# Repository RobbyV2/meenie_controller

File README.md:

# Meenie Controller

Meenie is a USB-C controller board. The board has a Nordic nRF52840 microcontroller. The board has Bluetooth Low Energy, USB 2.0 data, and 15 GPIO breakout holes. The board has one red status LED and one reset switch. The board has three service lands for SWDIO, SWCLK, and +3V3.

<table>
<tr>
<td></td>
<td></td>
<td></td>
</tr>
</table>

## Specifications

| Item | Value |
|---|---|
| Board size | 13.570 x 9.435 mm |
| Copper layers | 8, in a 3+2+3 sequential HDI stack |
| Finished thickness | 0.991 mm, quoted as a nominal 1.0 mm |
| Microcontroller | Nordic nRF52840-QIAA, aQFN-73, on B.Cu |
| Connector | 16-position USB-C sink receptacle on F.Cu |
| Antenna | Locked track on the F.Cu layer at the west edge |
| Reset switch | C&K NanoT `GSNANOT000102` on B.Cu |
| Surface finish | ENIG |
| Panel | 5 x 7, 35 boards, 89.850 x 92.045 mm |

Read `docs/design.md` for the full stack table and the via inventory.

The short axis of the board is 9.435 mm. NextPCB, for example, has a minimum board size is 10 x 10 mm.

## Repository layout

- `hw/` holds the KiCad schematic, the board, the design rules, and the stack manifest.
- `lib/` holds the symbols, the footprints, and the 3D models.
- `scripts/` holds the release script, the panel tools, and the validation scripts.
- `fab/` holds the fabrication data, written by `scripts/release.sh`.
- `docs/` holds the design specification and the vendor order gate.
- `3d/` holds the 3D build script, the three renders, and the viewer page.

## Build the 3D output
```
python3 3d/build.py
```

## Build the fabrication tree
```
MEENIE_DRY_RUN=1 scripts/release.sh hw/meenie.kicad_pcb
```

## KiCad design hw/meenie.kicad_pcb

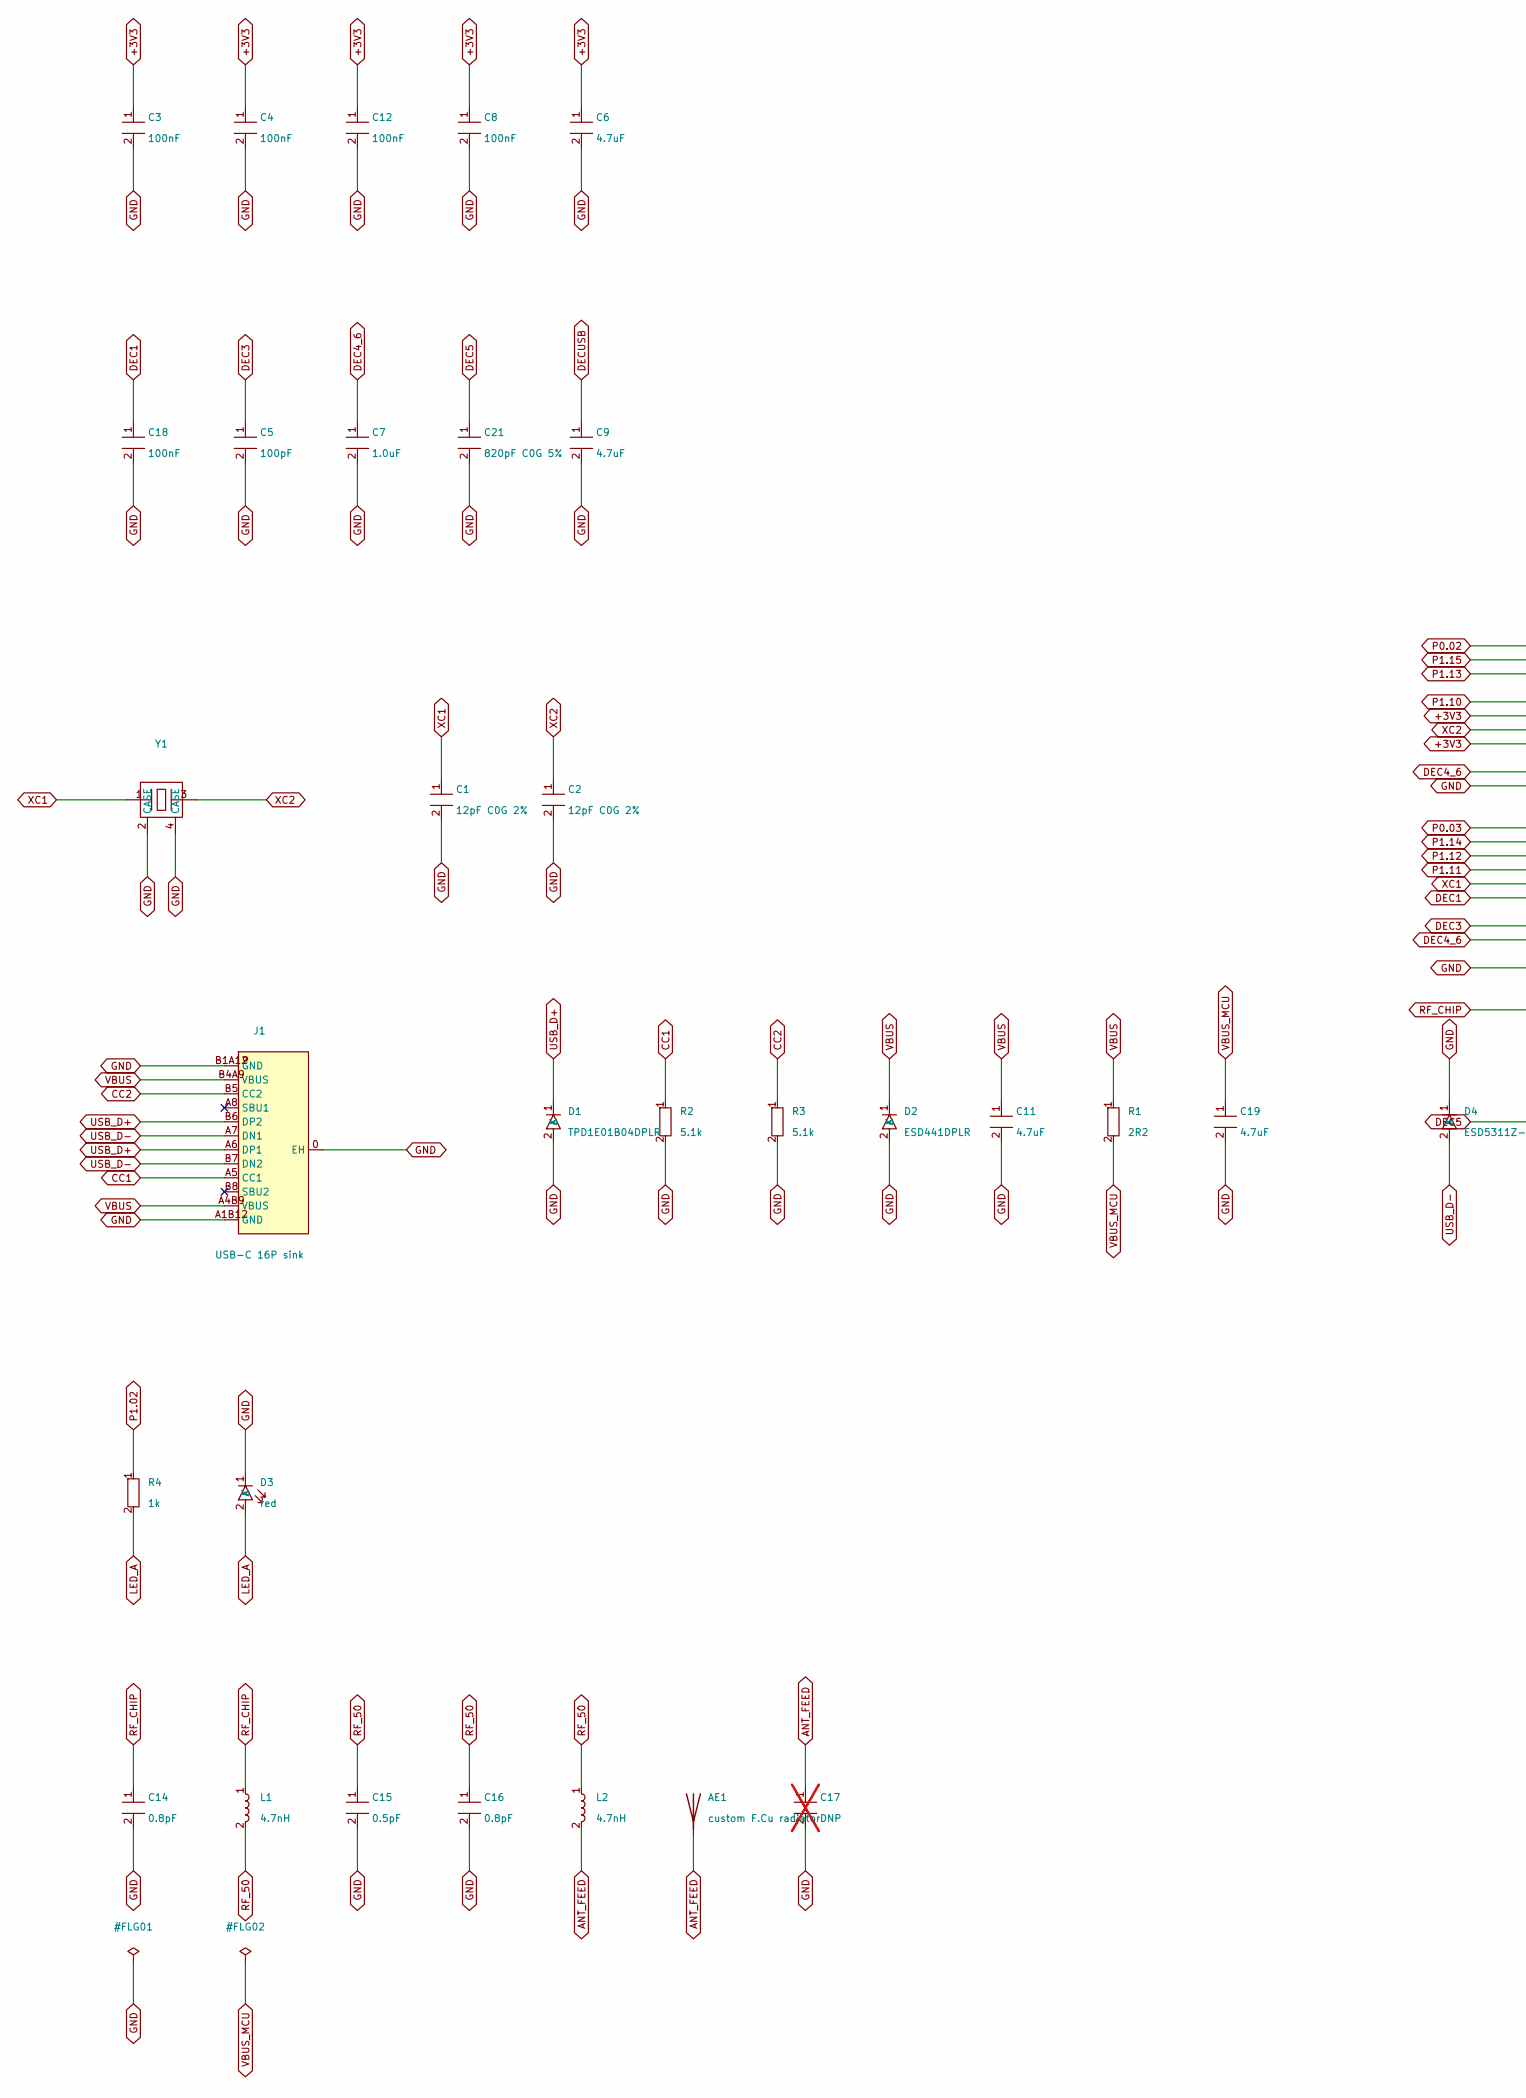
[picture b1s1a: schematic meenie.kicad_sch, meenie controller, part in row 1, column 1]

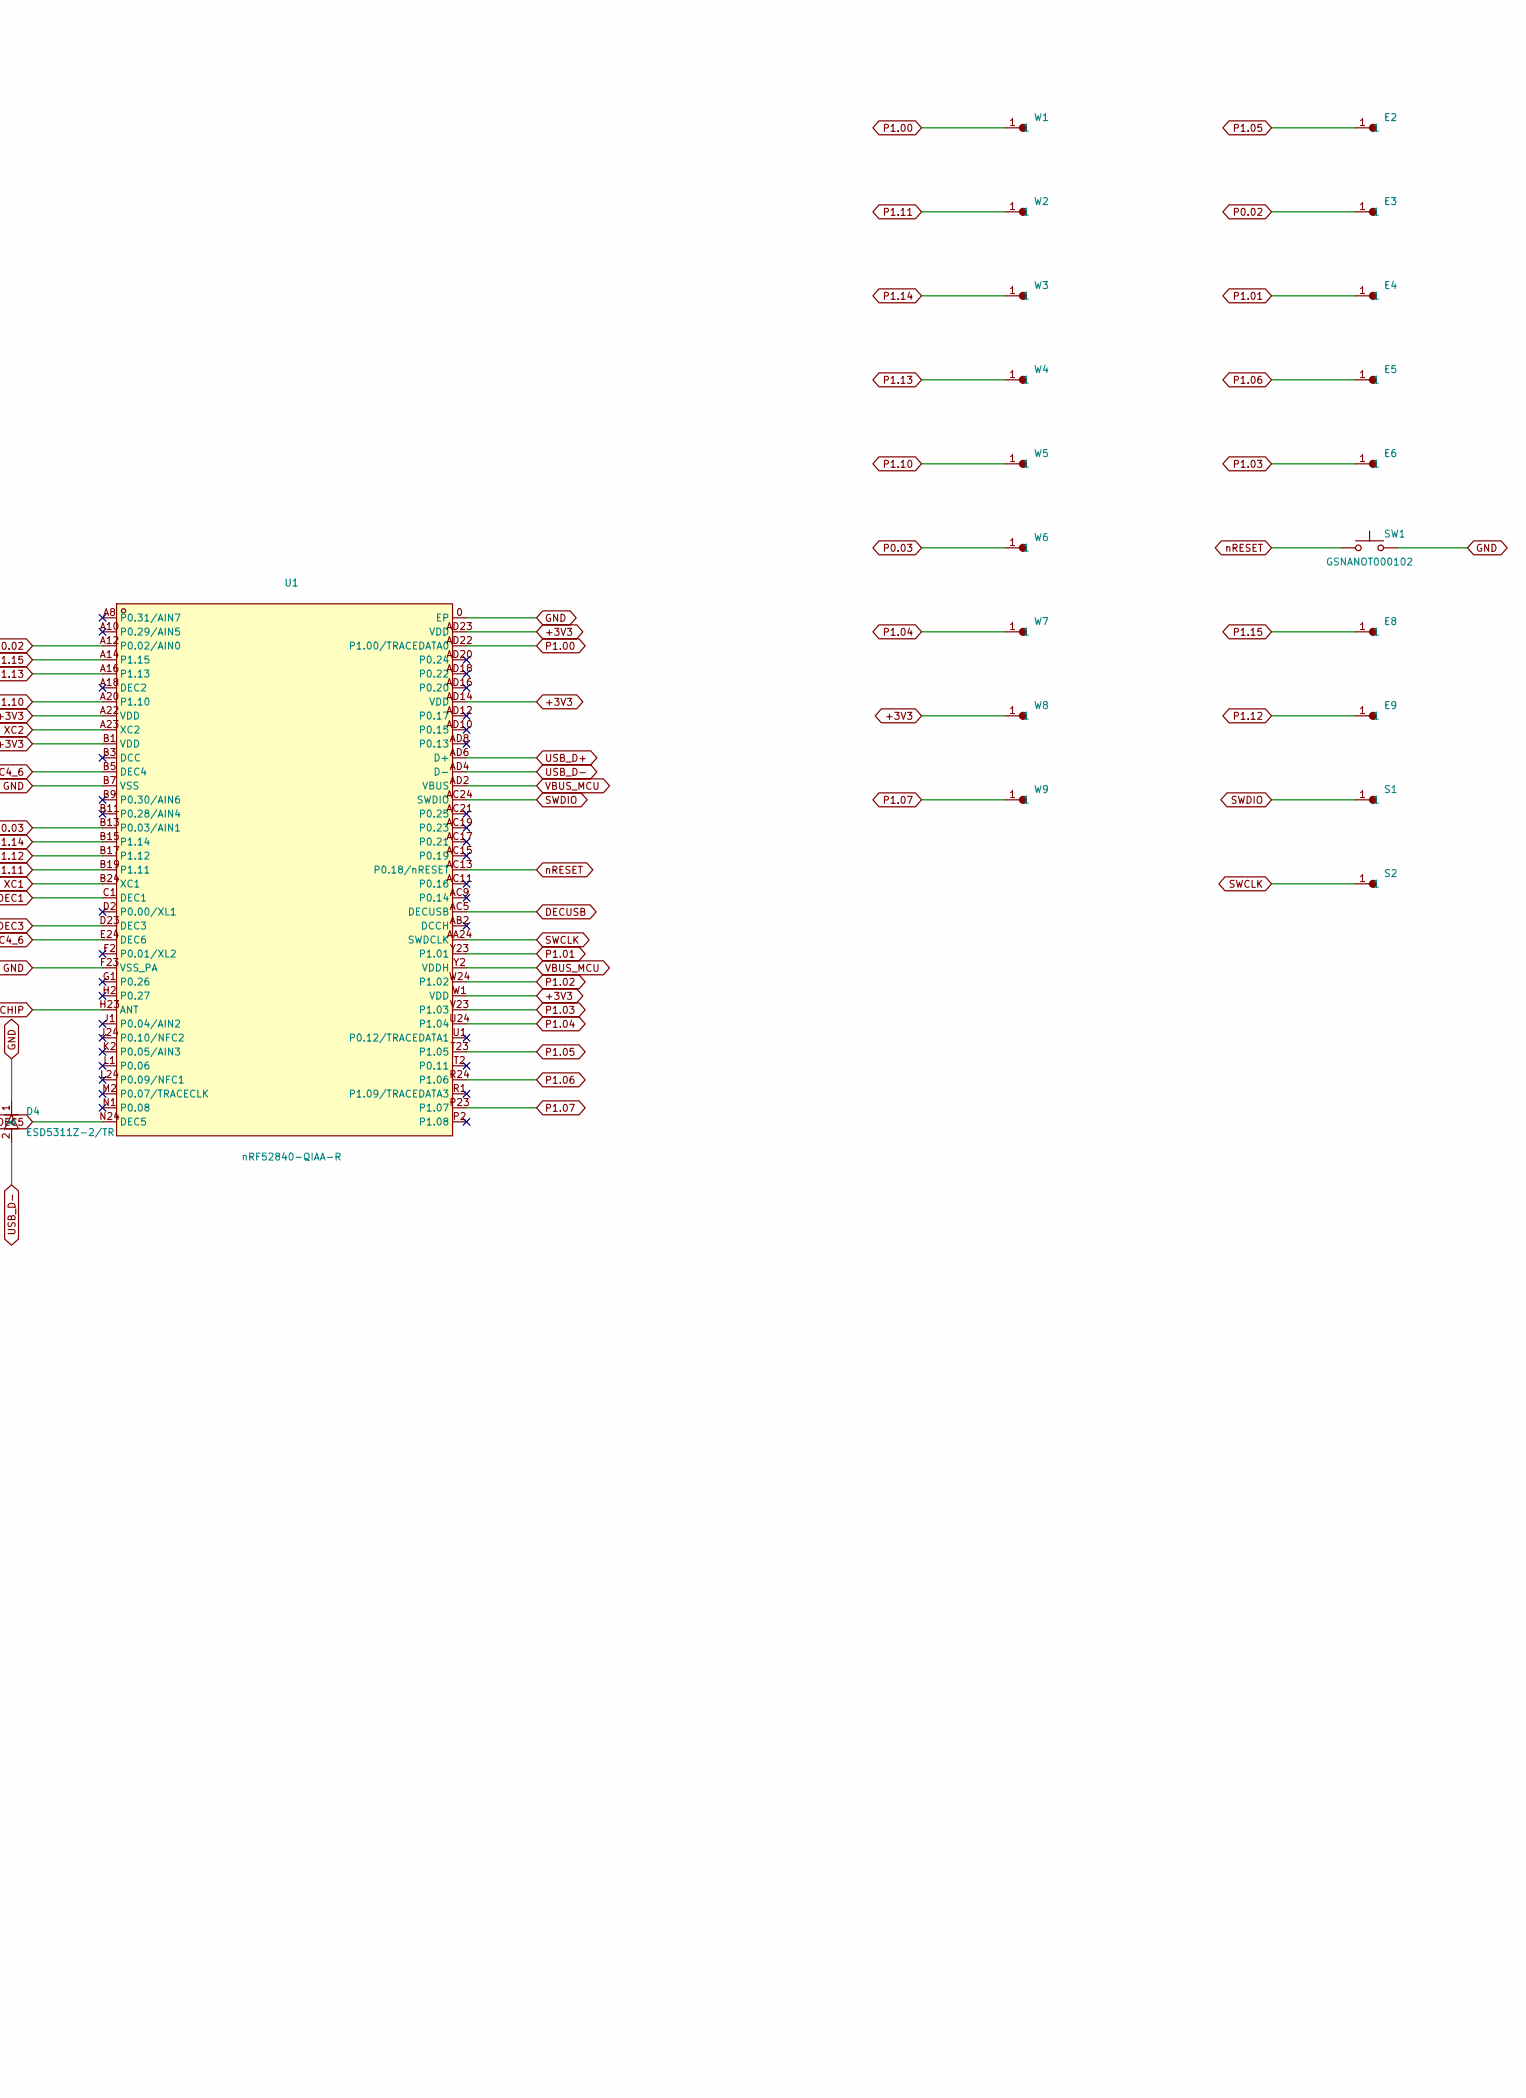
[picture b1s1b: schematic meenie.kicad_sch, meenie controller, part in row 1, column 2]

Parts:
AE1: custom F.Cu radiator
C1, C2: 12pF C0G 2%; C0201; MPN GRM0335C1H120GA01D; LCSC Part C161404
C3, C12, C18: 100nF; C0201; MPN GRM033C71C104KE14D; LCSC Part C85923
C4: 100nF; C0201_Murata_GRM033; MPN GRM033C71C104KE14D; LCSC Part C85923
C5: 100pF; C0201; MPN CC0201JRNPO9BN101; LCSC Part C272870
C6: 4.7uF; C0603; Manufacturer Part Number GRM188R61E475KE11D; LCSC Part C90057
C7: 1.0uF; C0402; MPN CL05A105KA5NQNC; LCSC Part C52923
C8: 100nF; C0402; Manufacturer Part Number CL05B104KO5NNNC; LCSC Part C1525
C9, C11: 4.7uF; C0603; MPN GRM188R61E475KE11D; LCSC Part C90057
C14, C16: 0.8pF; C0201; MPN GJM0335C1ER80WB01D; LCSC Part C408126
C15: 0.5pF; C0201; MPN GJM0335C1HR50WB01D; LCSC Part C237424
C17: DNP; C0201; LCSC Part NOT SELECTED; not fitted
C19: 4.7uF; C0402; Manufacturer Part Number CL05A475MO5NUNC; LCSC Part C318563
C21: 820pF C0G 5%; C0201; MPN GRM0335C1E821JA01D; LCSC Part C384953
D1: TPD1E01B04DPLR; ESD_X2SON_DPL; MPN TPD1E01B04DPLR; LCSC Part C1972949
D2: ESD441DPLR; ESD_X2SON_DPL; MPN ESD441DPLR; LCSC Part C22427765
D3: red; LED0402-R-RD_RED; MPN LTST-C281KRKT; LCSC Part C364556
D4: ESD5311Z-2/TR; ESD_DFN0603-2; MPN ESD5311Z-2/TR; LCSC Part C239819
E2, E3, E4, E5, E6, E8, E9: pad; TestPad_0.6mm_PTH
J1: USB-C 16P sink; USB-TYPE-C-SMD_TYPE-C-16P-QTWT; MPN TYPE-C 16P QTWT; LCSC Part C5187472
L1, L2: 4.7nH; L0201; MPN LQP03HQ4N7H02D; LCSC Part C237443
R1: 2R2; R0402; MPN RC0402FR-072R2L; LCSC Part C327251
R2, R3: 5.1k; R0201; MPN RC0201FR-075K1L; LCSC Part C274341
R4: 1k; R0201; MPN 0201WMF1001TEE; LCSC Part C270365
S1, S2: pad; TestPad_0.6mm
SW1: GSNANOT000102; Switch_NanoT_AS; MPN GSNANOT000102; DigiKey Part 108-NANOT160ASCT-ND
U1: nRF52840-QIAA-R; AQFN-73_L7.0-W7.0-P0.50-BL-EP4.8; MPN NRF52840-QIAA-R; LCSC Part C190794
W1, W2, W3, W4, W5, W6, W7, W9: pad; TestPad_0.6mm_PTH
W8: pad; TestPad_0.6mm
Y1: FA-118T 32MHz CL 8pF; Crystal_SMD_1612-4Pin_FA-118T; MPN X1E0002510059; LCSC Part C255986

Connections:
+3V3: C3.1, C4.1, C6.1, C8.1, C12.1, U1.A22 (VDD), U1.AD14 (VDD), U1.AD23 (VDD), U1.B1 (VDD), U1.W1 (VDD), W8.1
ANT_FEED: AE1.1, C17.1, L2.2
CC1: J1.A5 (CC1), R2.1
CC2: J1.B5 (CC2), R3.1
DEC1: C18.1, U1.C1 (DEC1)
DEC3: C5.1, U1.D23 (DEC3)
DEC4_6: C7.1, U1.B5 (DEC4), U1.E24 (DEC6)
DEC5: C21.1, U1.N24 (DEC5)
DECUSB: C9.1, U1.AC5 (DECUSB)
GND: C1.2, C2.2, C3.2, C4.2, C5.2, C6.2, C7.2, C8.2, C9.2, C11.2, C12.2, C14.2, C15.2, C16.2, C17.2, C18.2, C19.2, C21.2, D1.2 (A), D2.2 (A), D3.1 (K), D4.1 (K), J1.0 (EH), J1.A1B12 (GND), J1.B1A12 (GND), R2.2, R3.2, SW1.2, U1.0 (EP), U1.B7 (VSS), U1.F23 (VSS_PA), Y1.2 (CASE), Y1.4 (CASE)
LED_A: D3.2 (A), R4.2
P0.02: E3.1, U1.A12 (P0.02/AIN0)
P0.03: U1.B13 (P0.03/AIN1), W6.1
P1.00: U1.AD22 (P1.00/TRACEDATA0), W1.1
P1.01: E4.1, U1.Y23 (P1.01)
P1.02: R4.1, U1.W24 (P1.02)
P1.03: E6.1, U1.V23 (P1.03)
P1.04: U1.U24 (P1.04), W7.1
P1.05: E2.1, U1.T23 (P1.05)
P1.06: E5.1, U1.R24 (P1.06)
P1.07: U1.P23 (P1.07), W9.1
P1.10: U1.A20 (P1.10), W5.1
P1.11: U1.B19 (P1.11), W2.1
P1.12: E9.1, U1.B17 (P1.12)
P1.13: U1.A16 (P1.13), W4.1
P1.14: U1.B15 (P1.14), W3.1
P1.15: E8.1, U1.A14 (P1.15)
RF_50: C15.1, C16.1, L1.2, L2.1
RF_CHIP: C14.1, L1.1, U1.H23 (ANT)
SWCLK: S2.1, U1.AA24 (SWDCLK)
SWDIO: S1.1, U1.AC24 (SWDIO)
USB_D+: D1.1 (K), J1.A6 (DP1), J1.B6 (DP2), U1.AD6 (D+)
USB_D-: D4.2 (A), J1.A7 (DN1), J1.B7 (DN2), U1.AD4 (D-)
VBUS: C11.1, D2.1 (K), J1.A4B9 (VBUS), J1.B4A9 (VBUS), R1.1
VBUS_MCU: C19.1, R1.2, U1.AD2 (VBUS), U1.Y2 (VDDH)
XC1: C1.1, U1.B24 (XC1), Y1.1
XC2: C2.1, U1.A23 (XC2), Y1.3
nRESET: SW1.1, U1.AC13 (P0.18/nRESET)

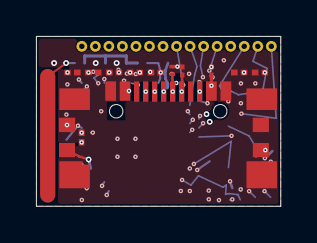
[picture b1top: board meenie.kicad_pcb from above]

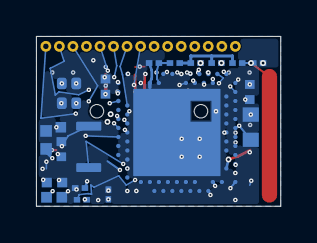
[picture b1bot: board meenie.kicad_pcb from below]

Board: 8 copper layers, 13.6 x 9.4 mm, 50 parts (22 on the bottom side), 38 nets.
